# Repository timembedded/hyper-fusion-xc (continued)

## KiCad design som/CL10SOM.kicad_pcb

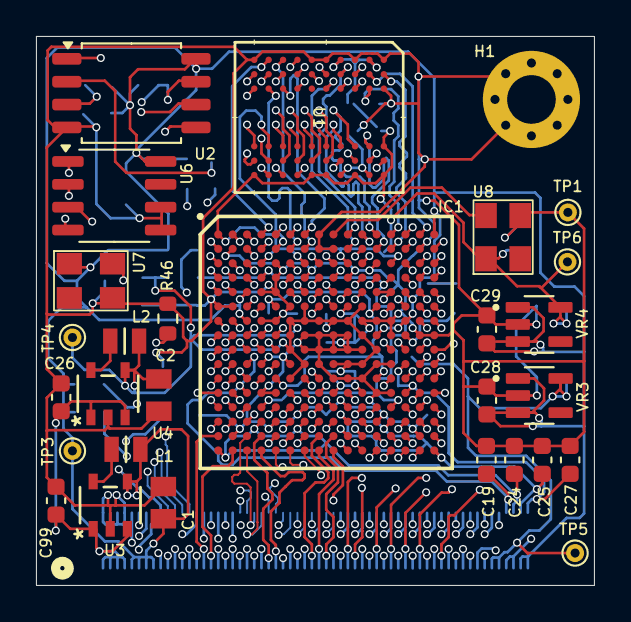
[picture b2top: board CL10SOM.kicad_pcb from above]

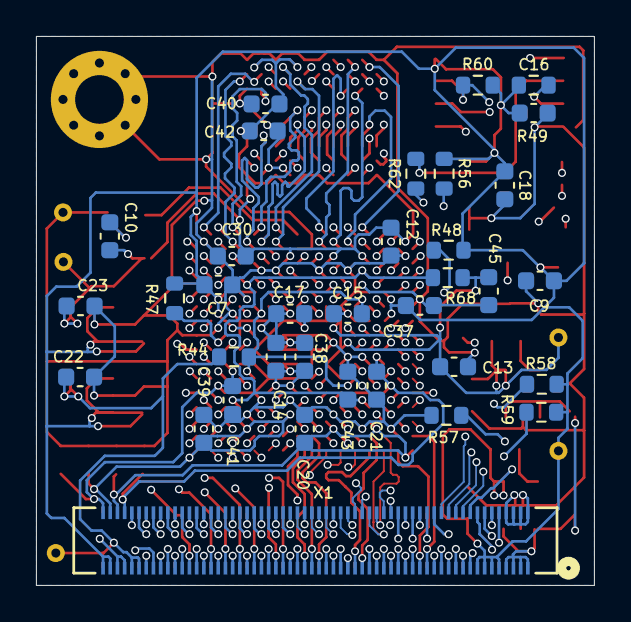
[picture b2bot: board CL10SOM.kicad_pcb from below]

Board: 4 copper layers, 31.0 x 30.5 mm, 64 parts (35 on the bottom side), 171 nets.

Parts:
C1, C2: GRM21BR60J226ME39L; CAPC2012X140N
C7, C9, C10, C12, C13, C14, C15, C16, C17, C18, C19, C20, C21, C24, C25, C27, C30, C37, C38, C39, C40, C41, C42, C43, C45: 100nF; C_0603_1608Metric
C22, C23, C28, C29: 2.2uF; C_0603_1608Metric
C26, C99: 4.7uF; C_0603_1608Metric
H1: MountingHole_Pad; MountingHole_2.7mm_M2.5_Pad_Via
IC1: 10CL025YU256C8G; BGA256C80P16X16_1400X1400X150
L1, L2: DFE21CCN1R0MELL; MURATA_DFE21CCN1R0MELL_0
R44, R68: 10E; R_0603_1608Metric
R46, R47, R48, R49, R56, R58, R59, R60: 10k; R_0603_1608Metric
R57: 1k; R_0603_1608Metric
R62: 24E9; R_0603_1608Metric
TP1, TP3, TP4, TP5, TP6: TestPoint; TestPoint_THTPad_D1.0mm_Drill0.5mm
U1: MT46H32M16LFBF-5 IT:C; MIC-VFBGA-60-BF_MRN
U2: MX25L12833FM2; SOIC-8_5.3x5.3mm_P1.27mm
U3: SC189ZSKTRT; SOT23-5-SC189_SEM
U4: SC189CSKTRT; SOT_CSKTRT_SEM
U6: AT93C46DN-SH-T; SO-8_3.9x4.9mm_P1.27mm
U7, U8: SG3225CAN 50.0000M-TJGA6; SG3225CAN
VR3: AP7366EA-25W5-7; SOT95P285X140-5N
VR4: AP7366EA-18W5-7; SOT95P285X140-5N
X1: DF40C-120DS-0.4V51; CONN_DF40C-120DS-0.4V51_HIR

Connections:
+1V2: C2.1, C13.1, C14.1, C17.1, C38.1, C45.1, IC1.F7 (VCCINT_1), IC1.F11 (VCCINT_2), IC1.G6 (VCCINT_3), IC1.G7 (VCCINT_4), IC1.G8 (VCCINT_5), IC1.G9 (VCCINT_6), IC1.G10 (VCCINT_7), IC1.H6 (VCCINT_8), IC1.H11 (VCCINT_9), IC1.J6 (VCCINT_10), IC1.J12 (VCCINT_11), IC1.K7 (VCCINT_12), IC1.K9 (VCCINT_13), IC1.K10 (VCCINT_14), IC1.K11 (VCCINT_15), IC1.L6 (VCCINT_16), IC1.M9 (VCCINT_17), IC1.M11 (VCCINT_18), L2.2, R68.1, TP4.1, U4.4 (VOUT(1.2V))
+1V8: C10.2, C12.1, C23.2, C30.2, C40.1, C42.1, IC1.A1 (VCCIO8_1), IC1.C4 (VCCIO8_2), IC1.C7 (VCCIO8_3), IC1.C10 (VCCIO7_2), IC1.C13 (VCCIO7_3), TP6.1, U1.A7 (VDDQ), U1.A9 (VDD), U1.B1 (VDDQ), U1.C9 (VDDQ), U1.D1 (VDDQ), U1.E9 (VDDQ), U1.F9 (VDD), U1.K9 (VDD), U8.4 (VCC), VR4.5 (OUT), X1.113, X1.115
+2V5: C22.2, R44.1, TP5.1, VR3.5 (OUT), X1.17, X1.109, X1.111
+3V3: C1.1, C7.1, C9.2, C16.1, C18.1, C28.2, C29.2, C37.1, IC1.A16 (VCCIO7_1), IC1.E3 (VCCIO1_1), IC1.E14 (VCCIO6_1), IC1.G3 (VCCIO1_2), IC1.G14 (VCCIO6_2), IC1.H12 (MSEL1), L1.2, R47.2, R48.1, R49.2, R56.1, R58.1, R59.1, R60.2, TP3.1, U2.8 (VCC), U3.4 (VOUT(3.3V)), U6.8 (VCC), U7.4 (VCC), VR3.1 (IN), VR3.3 (EN), VR4.1 (IN), VR4.3 (EN), X1.9, X1.11, X1.13, X1.15, X1.117, X1.119
+5V: C26.2, C99.2, U3.1 (VIN), U3.3 (EN), U4.1 (VIN), U4.3 (EN), X1.1, X1.3, X1.5, X1.7
/ASDO: IC1.C1 (IO/DIFFIO_L3n/DATA1,ASDO), U2.5 (SI/SIO0)
/B1-CLK1: IC1.E1 (CLK1/DIFFCLK_0n), X1.18
/B2-CLK2: IC1.M2 (CLK2/DIFFCLK_1p), X1.25
/B2-CLK3: IC1.M1 (CLK3/DIFFCLK_1n), X1.23
/B2-IO1N: IC1.J1 (IO/DIFFIO_L7n), X1.20
/B2-IO1P: IC1.J2 (IO/DIFFIO_L7p), X1.22
/B2-IO2N: IC1.K1 (IO/DIFFIO_L10n), X1.24
/B2-IO2P: IC1.K2 (IO/DIFFIO_L10p), X1.26
/B2-IO3N: IC1.L1 (IO/DIFFIO_L11n), X1.28
/B2-IO3P: IC1.L2 (IO/DIFFIO_L11p/DPCLK1), X1.30
/B2-IO4: IC1.L3 (IO/VREFB2N0), X1.21
/B2-IO5N: IC1.N1 (IO/DIFFIO_L13n), X1.32
/B2-IO5P: IC1.N2 (IO/DIFFIO_L13p), X1.34
/B2-IO6: IC1.K5 (IO/RUP1), X1.19
/B2-IO7: IC1.L4 (IO/RDN1), X1.27
/B2-IO8: IC1.R1 (IO/CDPCLK1), X1.29
/B2-IO9N: IC1.P1 (IO/DIFFIO_L15n), X1.36
/B2-IO9P: IC1.P2 (IO/DIFFIO_L15p), X1.38
/B3-CLK14: IC1.T8 (CLK14/DIFFCLK_6n), X1.61
/B3-CLK15: IC1.R8 (CLK15/DIFFCLK_6p), X1.59
/B3-IO1N: IC1.P3 (IO/DIFFIO_B1n), X1.42
/B3-IO1P: IC1.N3 (IO/DIFFIO_B1p), X1.40
/B3-IO2N: IC1.T3 (IO/DIFFIO_B2n), X1.46
/B3-IO2P: IC1.R3 (IO/DIFFIO_B2p), X1.44
/B3-IO3: IC1.T2 (IO/CDPCLK2), X1.31
/B3-IO4-CON: IC1.T4 (IO/PLL1_CLKOUTn), X1.49
/B3-IO4-COP: IC1.R4 (IO/PLL1_CLKOUTp), X1.47
/B3-IO6N: IC1.N6 (IO/DIFFIO_B4n), X1.50
/B3-IO6P: IC1.N5 (IO/DIFFIO_B4p), X1.48
/B3-IO7: IC1.M6 (IO), X1.37
/B3-IO8: IC1.P6 (IO/VREFB3N0), X1.39
/B3-IO9: IC1.M7 (IO/DIFFIO_B5p/DPCLK2), X1.41
/B3-IO10N: IC1.T5 (IO/DIFFIO_B6n), X1.54
/B3-IO10P: IC1.R5 (IO/DIFFIO_B6p), X1.52
/B3-IO11N: IC1.T6 (IO/DIFFIO_B7n), X1.58
/B3-IO11P: IC1.R6 (IO/DIFFIO_B7p), X1.56
/B3-IO12: IC1.L7 (IO), X1.35
/B3-IO13N: IC1.T7 (IO/DIFFIO_B8n/DPCLK3), X1.62
/B3-IO13P: IC1.R7 (IO/DIFFIO_B8p), X1.60
/B3-IO14: IC1.L8 (IO/DIFFIO_B9n), X1.33
/B3-IO15: IC1.M8 (IO/DIFFIO_B10n), X1.51
/B3-IO16: IC1.N8 (IO/DIFFIO_B11p), X1.43
/B3-IO17: IC1.P8 (IO/DIFFIO_B12n), X1.45
/B4-CLK12: IC1.T9 (CLK12/DIFFCLK_7n), X1.65
/B4-CLK13: IC1.R9 (CLK13/DIFFCLK_7p), X1.63
/B4-IO1: IC1.N9 (IO/DIFFIO_B14n), X1.55
/B4-IO2N: IC1.T10 (IO/DIFFIO_B16n), X1.66
/B4-IO2P: IC1.R10 (IO/DIFFIO_B16p), X1.64
/B4-IO3N: IC1.T11 (IO/DIFFIO_B17n), X1.70
/B4-IO3P: IC1.R11 (IO/DIFFIO_B17p), X1.68
/B4-IO4N: IC1.T12 (IO/DIFFIO_B18n), X1.74
/B4-IO4P: IC1.R12 (IO/DIFFIO_B18p), X1.72
/B4-IO5: IC1.P9 (IO/DPCLK5), X1.53
/B4-IO6: IC1.P11 (IO/VREFB4N0), X1.69
/B4-IO7N: IC1.T13 (IO/DIFFIO_B20n), X1.78
/B4-IO7P: IC1.R13 (IO/DIFFIO_B20p), X1.76
/B4-IO8: IC1.M10 (IO/RUP2), X1.57
/B4-IO9: IC1.N11 (IO/RDN2), X1.67
/B4-IO10N: IC1.T15 (IO/DIFFIO_B23n), X1.82
/B4-IO10P: IC1.T14 (IO/DIFFIO_B23p), X1.80
/B4-IO11: IC1.N12 (IO/DIFFIO_B24p), X1.71
/B4-IO12-CON: IC1.R14 (IO/PLL4_CLKOUTn), X1.86
/B4-IO12-COP: IC1.P14 (IO/PLL4_CLKOUTp), X1.84
/B5-CLK6: IC1.M15 (CLK6/DIFFCLK_3p), X1.79
/B5-CLK7: IC1.M16 (CLK7/DIFFCLK_3n), X1.81
/B5-IO1: IC1.N14 (IO/RUP3), X1.75
/B5-IO2: IC1.P15 (IO/RDN3), X1.77
/B5-IO3N: IC1.P16 (IO/DIFFIO_R15n/CDPCLK4), X1.94
/B5-IO3P: IC1.R16 (IO/DIFFIO_R15p), X1.92
/B5-IO4N: IC1.N16 (IO/DIFFIO_R13n), X1.90
/B5-IO4P: IC1.N15 (IO/DIFFIO_R13p), X1.88
/B5-IO5: IC1.L14 (IO/VREFB5N0), X1.83
/B5-IO6: IC1.L13 (IO/DIFFIO_R12p), X1.73
/B5-IO7N: IC1.L16 (IO/DIFFIO_R11n), X1.98
/B5-IO7P: IC1.L15 (IO/DIFFIO_R11p), X1.96
/B5-IO8N: IC1.K16 (IO/DIFFIO_R10n), X1.102
/B5-IO8P: IC1.K15 (IO/DIFFIO_R10p), X1.100
/B5-IO9N: IC1.J16 (IO/DIFFIO_R9n), X1.106
/B5-IO9P: IC1.J15 (IO/DIFFIO_R9p), X1.104
/B5-IO10: IC1.J14 (IO/DIFFIO_R8n), X1.87
/B5-IO11: IC1.J13 (IO/DIFFIO_R7n), X1.85
/B6-CLK4: IC1.E15 (CLK4/DIFFCLK_2p), X1.99
/B6-CLK5: IC1.E16 (CLK5/DIFFCLK_2n), X1.97
/B6-IO1N: IC1.G16 (IO/DIFFIO_R5n/INIT_DONE), X1.110
/B6-IO1P: IC1.G15 (IO/DIFFIO_R5p/CRC_ERROR), X1.108
/B6-IO2: IC1.F13 (IO), X1.89
/B6-IO3: IC1.F16 (IO/DIFFIO_R4n/nCEO), X1.93
/B6-IO4: IC1.F15 (IO/DIFFIO_R4p/CLKUSR), X1.95
/B6-IO5: IC1.B16 (IO/DPCLK7), X1.105
/B6-IO6: IC1.F14 (IO/VREFB6N0), X1.91
/B6-IO7: IC1.D16 (IO), X1.103
/B6-IO8: IC1.D15 (IO), X1.101
/B6-IO9: IC1.C16 (IO/DIFFIO_R1n/CDPCLK5), X1.107
/B6-IO10: IC1.C15 (IO/DIFFIO_R1p), X1.112
/CLC50: IC1.E2 (CLK0/DIFFCLK_0p), U7.3 (OUT)
/CLCOPT: IC1.A9 (CLK8/DIFFCLK_5n), U8.3 (OUT)
/CONF_DONE: IC1.H14 (CONF_DONE), R47.1
/DATA0: IC1.H2 (IO/DATA0), R62.2
/DCLK: IC1.H1 (IO/DCLK), U2.6 (SCLK)
/DDR_A0: IC1.E8 (IO/DIFFIO_T10n/DATA2), U1.J8 (A0)
/DDR_A1: IC1.A5 (IO/DIFFIO_T5n/DATA7), U1.J9 (A1)
/DDR_A2: IC1.D6 (IO/DIFFIO_T4n), U1.K7 (A2)
/DDR_A3: IC1.E6 (IO/DIFFIO_T6p/DATA6), U1.K8 (A3)
/DDR_A4: IC1.A2 (IO/DIFFIO_T2n), U1.K2 (A4)
/DDR_A5: IC1.A3 (IO/DIFFIO_T2p), U1.K3 (A5)
/DDR_A6: IC1.A4 (IO/DIFFIO_T3n), U1.J1 (A6)
/DDR_A7: IC1.B3 (IO/CDPCLK7), U1.J2 (A7)
/DDR_A8: IC1.B6 (IO/DIFFIO_T7p), U1.J3 (A8)
/DDR_A9: IC1.B7 (IO/DIFFIO_T9p/DATA4), U1.H1 (A9)
/DDR_A10: IC1.B5 (IO/DIFFIO_T5p), U1.J7 (A10/AP)
/DDR_A11: IC1.B4 (IO/DIFFIO_T3p), U1.H2 (A11)
/DDR_A12: IC1.A7 (IO/DIFFIO_T9n), U1.H3 (A12)
/DDR_A13: IC1.F8 (IO/DIFFIO_T10p/DATA3), U1.F7 (A13)
/DDR_BA0: IC1.C6 (IO/VREFB8N0), U1.H8 (BA0)
/DDR_BA1: IC1.F9 (IO/DIFFIO_T17p/DPCLK8), U1.H9 (BA1)
/DDR_CKE: IC1.C8 (IO/DIFFIO_T11p/DPCLK10), U1.G1 (CKE)
/DDR_CLK: IC1.D3 (IO/PLL3_CLKOUTp), U1.G2 (CK)
/DDR_DM0: IC1.D9 (IO/DIFFIO_T15p), U1.F8 (LDM)
/DDR_DM1: IC1.D12 (IO/DIFFIO_T23p/CDPCLK6), U1.F2 (UDM)
/DDR_DQ0: IC1.C14 (IO/DIFFIO_T24n), U1.A8 (DQ0)
/DDR_DQ1: IC1.B12 (IO/DIFFIO_T21p), U1.B7 (DQ1)
/DDR_DQ2: IC1.D14 (IO/DIFFIO_T24p), U1.B8 (DQ2)
/DDR_DQ3: IC1.A12 (IO/DIFFIO_T21n), U1.C7 (DQ3)
/DDR_DQ4: IC1.B11 (IO/DIFFIO_T20p), U1.C8 (DQ4)
/DDR_DQ5: IC1.A11 (IO/DIFFIO_T20n), U1.D7 (DQ5)
/DDR_DQ6: IC1.E11 (IO/RUP4), U1.D8 (DQ6)
/DDR_DQ7: IC1.E10 (IO/RDN4), U1.E7 (DQ7)
/DDR_DQ8: IC1.B10 (IO/DIFFIO_T16p), U1.E3 (DQ8)
/DDR_DQ9: IC1.A10 (IO/DIFFIO_T16n), U1.D2 (DQ9)
/DDR_DQ10: IC1.C11 (IO/VREFB7N0), U1.D3 (DQ10)
/DDR_DQ11: IC1.B14 (IO/PLL2_CLKOUTp), U1.C2 (DQ11)
/DDR_DQ12: IC1.A14 (IO/PLL2_CLKOUTn), U1.C3 (DQ12)
/DDR_DQ13: IC1.A15 (IO/DIFFIO_T19n), U1.B2 (DQ13)
/DDR_DQ14: IC1.A13 (IO/DIFFIO_T22n), U1.B3 (DQ14)
/DDR_DQ15: IC1.B13 (IO/DIFFIO_T22p), U1.A2 (DQ15)
/DDR_DQS0: IC1.D11 (IO/DIFFIO_T23n), U1.E8 (LDQS)
/DDR_DQS1: IC1.C9 (IO/DIFFIO_T15n), U1.E2 (UDQS)
/EECK: IC1.C2 (IO/DIFFIO_L3p), U6.2 (SK)
/EECS: IC1.B1 (IO/CDPCLK0), U6.1 (CS)
/EEDI: IC1.D1 (IO/DIFFIO_L4n), U6.3 (DI)
/EEDO: IC1.F3 (IO/VREFB1N0), U6.4 (DO)
/FL_D2: IC1.G2 (IO/DIFFIO_L6p/DPCLK0), R49.1, U2.3 (~WP/SIO2)
/FL_D3: IC1.G1 (IO/DIFFIO_L6n), R60.1, U2.7 (~RESET/SIO3)
/TCK: IC1.H3 (TCK), R57.2, X1.12
/TDI: IC1.H4 (TDI), R59.2, X1.10
/TDO: IC1.J4 (TDO), X1.16
/TMS: IC1.J5 (TMS), R58.2, X1.14
/nCE: IC1.J3 (nCE), R46.2
/nCONFIG: IC1.H5 (nCONFIG), R48.2
/nCSO: IC1.D2 (IO/DIFFIO_L4p/FLASH_nCE,nCSO), U2.1 (~CS)
/nSTATUS: IC1.F4 (nSTATUS), R56.2
/~DDR_CAS: IC1.A6 (IO/DIFFIO_T7n/DPCLK11), U1.G8 (~CAS)
/~DDR_CLK: IC1.C3 (IO/PLL3_CLKOUTn), U1.G3 (~CK)
/~DDR_CS: IC1.E7 (IO/DATA5), U1.H7 (~CS)
/~DDR_RAS: IC1.D8 (IO), U1.G9 (~RAS)
/~DDR_WE: IC1.E9 (IO/DIFFIO_T13p/DPCLK9), U1.G7 (~WE)
GND: C1.2, C2.2, C7.2, C9.1, C10.1, C12.2, C13.2, C14.2, C15.2, C16.2, C17.2, C18.2, C19.2, C20.2, C21.2, C22.1, C23.1, C24.2, C25.2, C26.1, C27.2, C28.1, C29.1, C30.1, C37.2, C38.2, C39.2, C40.2, C41.2, C42.2, C43.2, C45.2, C99.1, H1.1, IC1.A8 (CLK10/DIFFCLK_4n), IC1.B2 (GND_1), IC1.B8 (CLK11/DIFFCLK_4p), IC1.B9 (CLK9/DIFFCLK_5p), IC1.B15 (GND_2), IC1.C5 (GND_3), IC1.C12 (GND_4), IC1.D5 (GND_5), IC1.D7 (GND_6), IC1.D10 (GND_7), IC1.E4 (GND_8), IC1.E5 (GNDA3), IC1.E12 (GNDA2), IC1.E13 (GND_9), IC1.F1 (GND_10), IC1.F2 (GND_11), IC1.F6 (GND_12), IC1.F10 (GND_13), IC1.G4 (GND_14), IC1.G5 (GND_15), IC1.G11 (GND_16), IC1.G12 (MSEL2), IC1.G13 (GND_17), IC1.H7 (GND_18), IC1.H8 (GND_19), IC1.H9 (GND_20), IC1.H10 (GND_21), IC1.H13 (MSEL0), IC1.H15 (GND_22), IC1.H16 (GND_23), IC1.J7 (GND_24), IC1.J8 (GND_25), IC1.J9 (GND_26), IC1.J10 (GND_27), IC1.J11 (GND_28), IC1.K4 (GND_29), IC1.K6 (GND_30), IC1.K8 (GND_31), IC1.K12 (GND_32), IC1.K13 (GND_33), IC1.L9 (GND_34), IC1.L10 (GND_35), IC1.L11 (GND_36), IC1.M4 (GND_37), IC1.M5 (GNDA1), IC1.M12 (GNDA4), IC1.M13 (GND_38), IC1.N7 (GND_39), IC1.N10 (GND_40), IC1.P5 (GND_41), IC1.P12 (GND_42), IC1.R2 (GND_43), IC1.R15 (GND_44), R46.1, R57.1, TP1.1, U1.A1 (VSS), U1.A3 (VSSQ), U1.B9 (VSSQ), U1.C1 (VSSQ), U1.D9 (TEST1), U1.E1 (VSSQ), U1.F1 (VSS), U1.K1 (VSS), U2.4 (GND), U3.2 (GND), U4.2 (GND), U6.5 (GND), U6.6 (ORG), U7.2 (GND), U8.2 (GND), VR3.2 (GND), VR4.2 (GND), X1.2, X1.4, X1.6, X1.8
unnamed: R62.1, U2.2 (SO/SIO1)
unnamed: L1.1, U3.5 (LX)
unnamed: L2.1, U4.5 (LX)
PLLA: C15.1, IC1.F5 (VCCA3), IC1.F12 (VCCA2), IC1.L5 (VCCA1), IC1.L12 (VCCA4), R44.2
PLLD: C43.1, IC1.D4 (VCCD_PLL3), IC1.D13 (VCCD_PLL2), IC1.N4 (VCCD_PLL1), IC1.N13 (VCCD_PLL4), R68.2
VCCB2: C19.1, C21.1, IC1.K3 (VCCIO2_1), IC1.M3 (VCCIO2_2), X1.114
VCCB3: C20.1, C24.1, IC1.P4 (VCCIO3_1), IC1.P7 (VCCIO3_2), IC1.T1 (VCCIO3_3), X1.116
VCCB4: C25.1, C39.1, IC1.P10 (VCCIO4_1), IC1.P13 (VCCIO4_2), IC1.T16 (VCCIO4_3), X1.118
VCCB5: C27.1, C41.1, IC1.K14 (VCCIO5_1), IC1.M14 (VCCIO5_2), X1.120

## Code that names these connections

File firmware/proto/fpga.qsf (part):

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set_location_assignment PIN_5 -to ADC_BCK
set_location_assignment PIN_8 -to ADC_SCKI
set_location_assignment PIN_10 -to ADC_LRCK
set_location_assignment PIN_12 -to EECS
set_location_assignment PIN_13 -to EECK
set_location_assignment PIN_14 -to EEDI
set_location_assignment PIN_15 -to EEDO
set_location_assignment PIN_27 -to pSltClk
set_location_assignment PIN_30 -to DAC_XSMT
set_location_assignment PIN_31 -to DAC_LRCK
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set_location_assignment PIN_168 -to pFlDat[4]
set_location_assignment PIN_169 -to pFlDat[3]
set_location_assignment PIN_170 -to SD_MISO
set_location_assignment PIN_171 -to SD_CLK
set_location_assignment PIN_173 -to SD_MOSI
set_location_assignment PIN_175 -to SD_CS
set_location_assignment PIN_176 -to HD01
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
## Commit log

2025-03-14 Work in progress schematic and PCB
2025-03-17 Work in progress
2025-04-09 SOM design baseline
2025-04-25 Placement change
2025-04-25 All I/O connected
2025-04-29 Some cleanup
2025-04-30 Use switching regulators for 3v3 and 1v2
2025-05-02 All routed, no errors
2025-05-02 Fixed warnings
2025-05-06 Improvements
2025-06-05 Use differential routing
2025-11-03 Added proto firmware
2025-11-11 ESP ipc interface work inprogress
2025-11-16 ESP audio example
2025-11-20 PSG emulation
2025-11-20 YM2413 emulation
2025-11-25 MsxAudio emulation
2025-11-26 Cleanup and restructuring
2025-11-26 Removed dead code from bluemsx code
2025-11-27 Attempt to use the other Y8950 implementation from bluemsx Not working
2025-12-10 ADPCM working nicely now
2025-12-17 Integrated Moonsound and optimized memory usage for buffers Moonsound not working yet because of performance issues
2025-12-23 Optimized YMF278 implementation
2025-12-23 Optimized LFO of YMF262
2025-12-28 Implemented dual-core execution
2025-12-28 Sound quality improvement
2025-12-30 Sample transition on zero crossing to prevent clicking sound
2025-12-30 Improved load reporting and reset
2025-12-30 Fixed performance issue
2025-12-30 Enhanced stereo
2026-01-01 Automatic mono/stereo switching for music+audio
2026-01-04 Added YM2413 implementation based on OpenMSX
2026-01-05 Implemented mute optimization in YM2413Burczynski
2026-01-09 Implemented SCC and keyclick sound generated in FPGA Removed YM2413 implementation from FPGA firmware
2026-01-09 Removed debug code
2026-01-16 Moved PSG implementation to FPGA
2026-01-26 Tighter slot timing for Turbo-R compatibility
2026-02-02 Schematic work in progress
2026-02-20 PCB work in progress
2026-03-26 Routing done
2026-04-17 Redesigned HDMI to solve obsolescence
